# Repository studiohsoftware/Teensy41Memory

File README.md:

# Teensy41Memory
64MB SPI Memory Board for Teensy 4.1
</br>
https://oshpark.com/shared_projects/a06G97QZ
</br>

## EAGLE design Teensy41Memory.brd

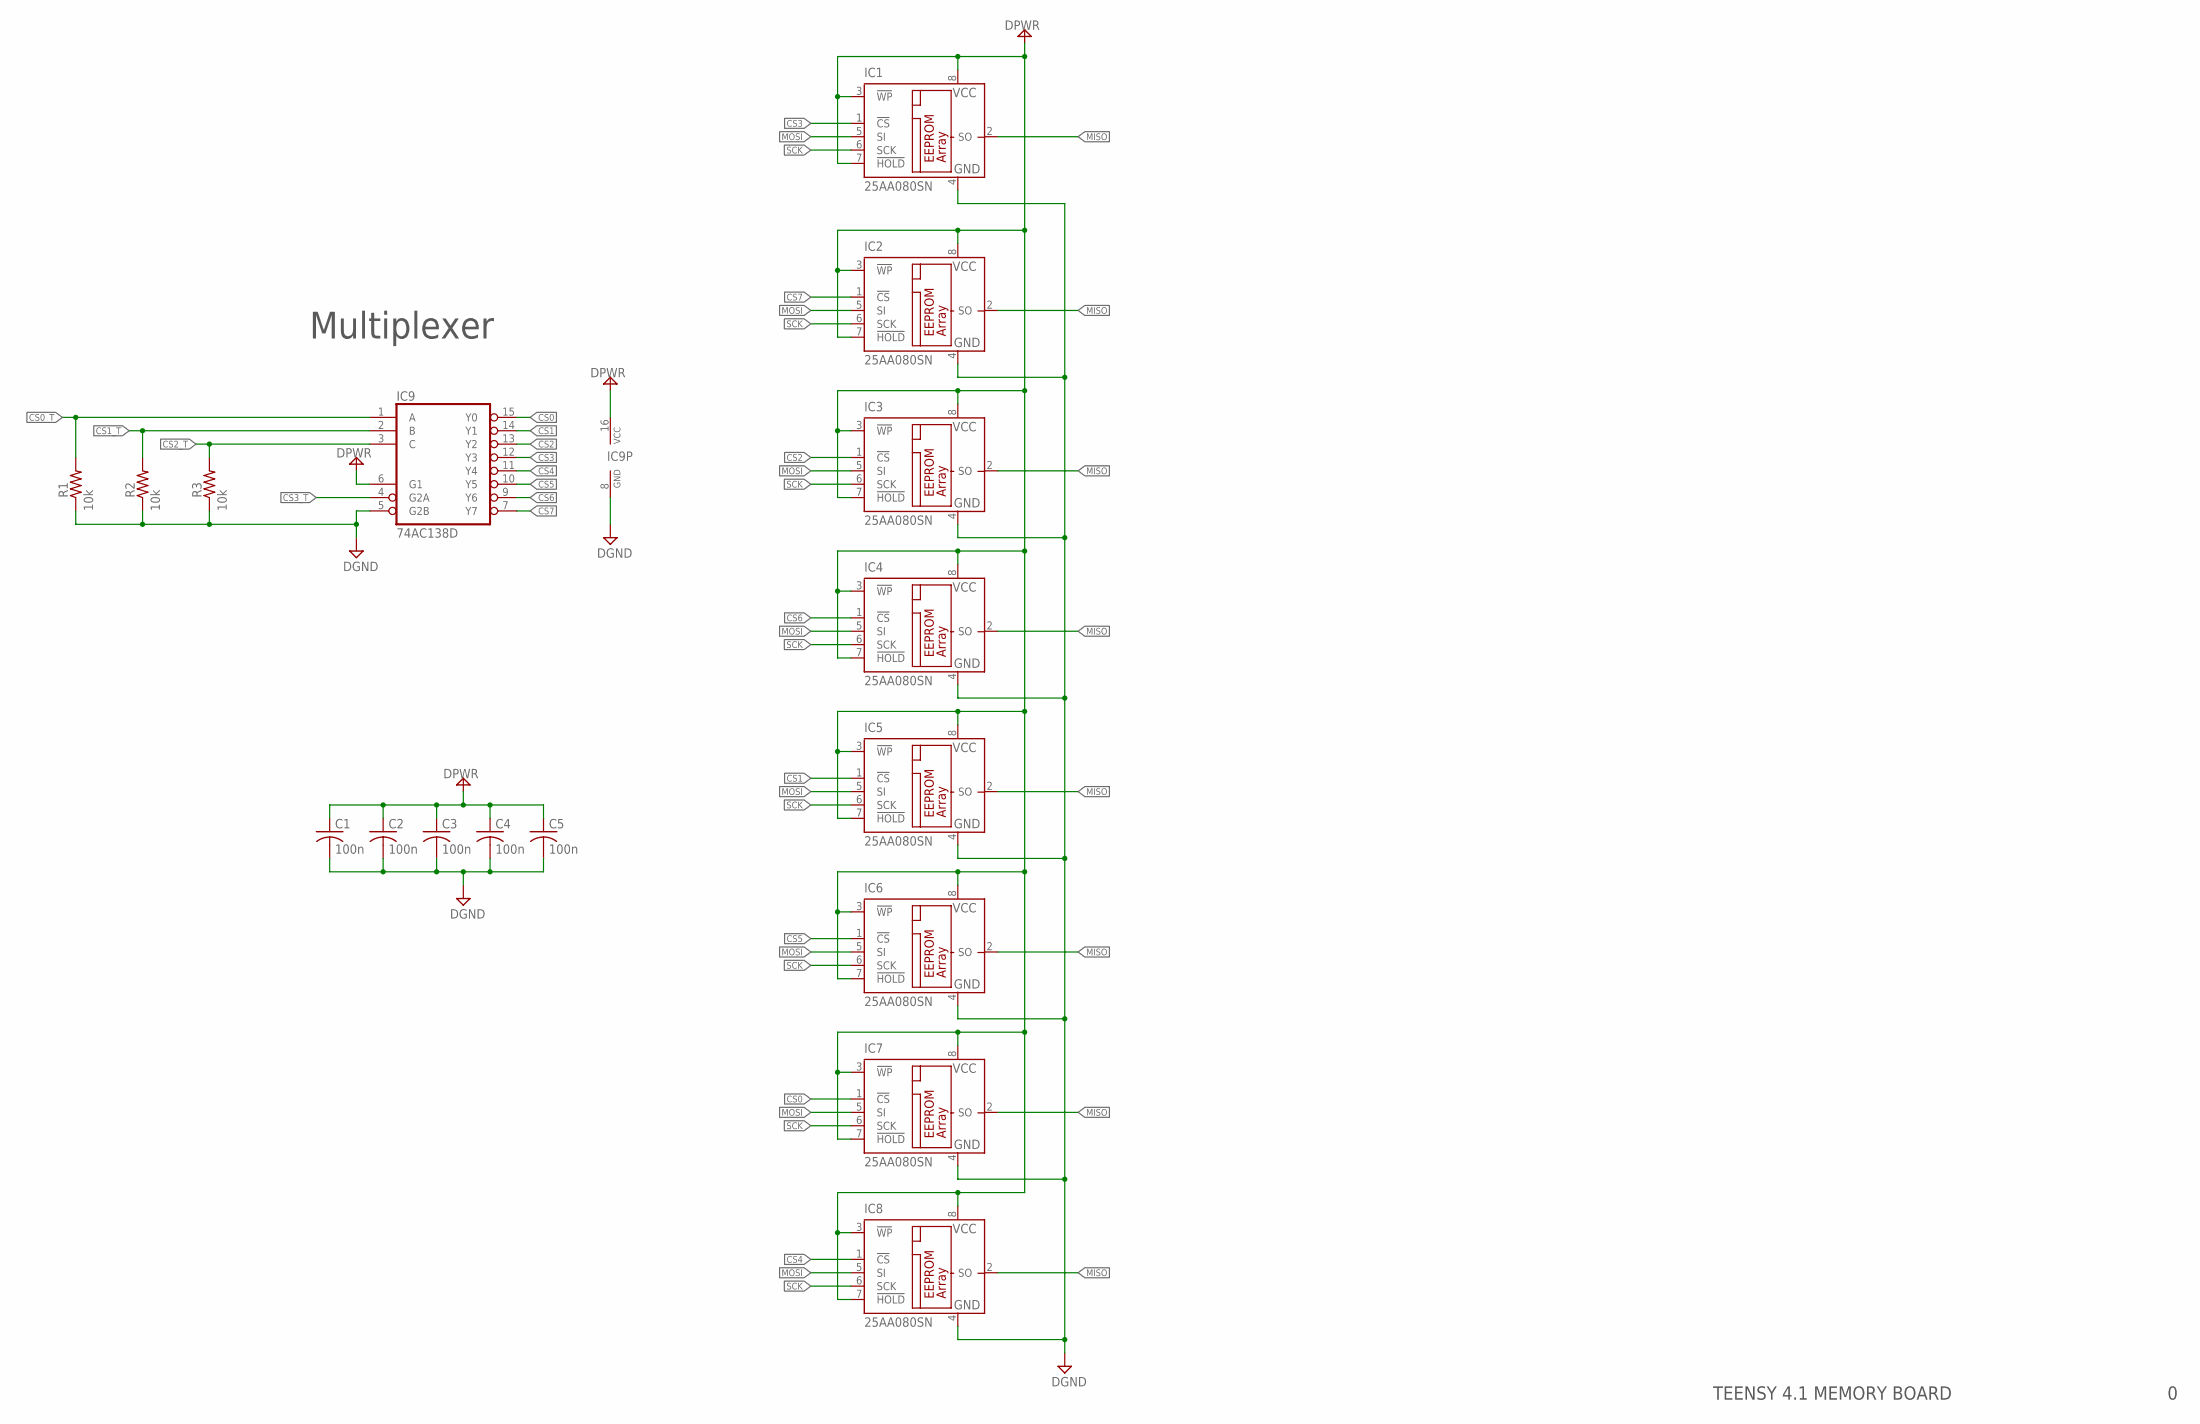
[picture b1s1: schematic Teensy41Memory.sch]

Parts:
C1, C2, C3, C4, C5: 100n; C0603
IC1, IC2, IC3, IC4, IC5, IC6, IC7, IC8: 25AA080SN; SO-08
IC9: 74AC138D; SO16
R1, R2, R3: 10k; R0603

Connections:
CS0: IC7.1 (!CS), IC9.15 (Y0)
CS0_T: IC9.1 (A), R1.2
CS1: IC5.1 (!CS), IC9.14 (Y1)
CS1_T: IC9.2 (B), R2.2
CS2: IC3.1 (!CS), IC9.13 (Y2)
CS2_T: IC9.3 (C), R3.2
CS3: IC1.1 (!CS), IC9.12 (Y3)
CS3_T: IC9.4 (G2A)
CS4: IC8.1 (!CS), IC9.11 (Y4)
CS5: IC6.1 (!CS), IC9.10 (Y5)
CS6: IC4.1 (!CS), IC9.9 (Y6)
CS7: IC2.1 (!CS), IC9.7 (Y7)
DGND: C1.2, C2.2, C3.2, C4.2, C5.2, IC1.4 (GND), IC2.4 (GND), IC3.4 (GND), IC4.4 (GND), IC5.4 (GND), IC6.4 (GND), IC7.4 (GND), IC8.4 (GND), IC9.5 (G2B), IC9.8 (GND), R1.1, R2.1, R3.1
DPWR: C1.1, C2.1, C3.1, C4.1, C5.1, IC1.3 (!WP), IC1.7 (!HOLD), IC1.8 (VCC), IC2.3 (!WP), IC2.7 (!HOLD), IC2.8 (VCC), IC3.3 (!WP), IC3.7 (!HOLD), IC3.8 (VCC), IC4.3 (!WP), IC4.7 (!HOLD), IC4.8 (VCC), IC5.3 (!WP), IC5.7 (!HOLD), IC5.8 (VCC), IC6.3 (!WP), IC6.7 (!HOLD), IC6.8 (VCC), IC7.3 (!WP), IC7.7 (!HOLD), IC7.8 (VCC), IC8.3 (!WP), IC8.7 (!HOLD), IC8.8 (VCC), IC9.6 (G1), IC9.16 (VCC)
MISO: IC1.2 (SO), IC2.2 (SO), IC3.2 (SO), IC4.2 (SO), IC5.2 (SO), IC6.2 (SO), IC7.2 (SO), IC8.2 (SO)
MOSI: IC1.5 (SI), IC2.5 (SI), IC3.5 (SI), IC4.5 (SI), IC5.5 (SI), IC6.5 (SI), IC7.5 (SI), IC8.5 (SI)
SCK: IC1.6 (SCK), IC2.6 (SCK), IC3.6 (SCK), IC4.6 (SCK), IC5.6 (SCK), IC6.6 (SCK), IC7.6 (SCK), IC8.6 (SCK)

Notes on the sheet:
Multiplexer
TEENSY 4.1 MEMORY BOARD

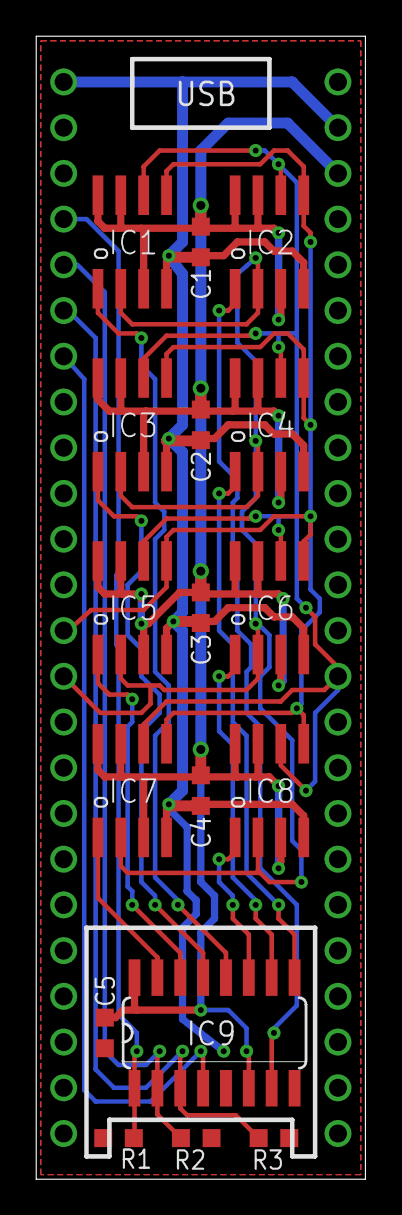
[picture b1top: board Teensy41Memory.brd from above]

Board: 2 copper layers, 18.3 x 63.5 mm, 275 parts (258 on the bottom side), 16 nets.

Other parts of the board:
U$1, U$8, U$10, U$17, U$27, U$38, U$140, U$144, U$151: A64CBI
U$2, U$11: W64CBI
U$3, U$12: V64CBI
U$4, U$5, U$13, U$14, U$25, U$34, U$124, U$131: E64CBI
U$6, U$15, U$39, U$75, U$135, U$146: S64CBI
U$7, U$16: H64CBI
U$9, U$18, U$123, U$130: P64CBI
U$19, U$28, U$118, U$125: M64CBI
U$20, U$29, U$99, U$119, U$126, U$142, U$145, U$153: O64CBI
U$21, U$24, U$30, U$33, U$120, U$127: D64CBI
U$22, U$31, U$137, U$148: I64CBI
U$23, U$32, U$41, U$77: N64CBI
U$26, U$35: X64CBI
U$36, U$37, U$155: B64CBI
U$40, U$76, U$122, U$129: Y64CBI
U$42, U$78, U$136, U$147: C64CBI
U$43, U$48, U$61, U$66, U$87, U$165, U$169, U$173, U$177: N64BI
U$44, U$47, U$54, U$62, U$65, U$68, U$92, U$96: O64BI
U$45, U$56, U$63, U$70: T64BI
U$46, U$64, U$84, U$86, U$91, U$103, U$112: E64BI
U$49, U$71: H64BI
U$50, U$72, U$88, U$101, U$104, U$110, U$113: A64BI
U$51, U$73, U$83: R64BI
U$52, U$74: D64BI
U$53, U$67, U$93, U$97: S64BI
U$55, U$69, U$107, U$116, U$162, U$170: F64BI
U$57, U$79: M54CBI
U$58, U$59, U$80, U$81: I54CBI
U$60, U$82: D54CBI
U$85, U$105, U$108, U$114, U$117, U$163, U$171: M64BI
U$89: B64BI
U$90: L64BI
U$94, U$98, U$166, U$174: C64BI
U$95: B54CBI
U$100, U$109: W64BI
U$102, U$111, U$167, U$175: V64BI
U$106, U$115: P64BI
U$121, U$128, U$141, U$152: T64CBI
U$132, U$133, U$156, U$157: CV-WHEEL-MED
U$134: A54CBI
U$138, U$139, U$149, U$150: L64CBI
U$143, U$154: R64CBI
U$158, U$160: CV-WHEEL-SM1
U$159, U$254: CV-WHEEL-LARGE
U$161: CV-WHEEL-SM2
U$164, U$168, U$172, U$176: I64BI
U$178, U$179, U$180, U$181, U$182, U$183, U$184, U$185, U$186, U$187, U$188, U$189, U$190, U$191, U$192, U$193, U$194, U$195, U$196, U$197, U$198, U$199, U$200, U$201, U$202, U$203, U$204, U$205, U$206, U$207, U$208, U$209, U$210, U$211, U$212, U$213, U$214, U$215, U$216, U$217, U$218, U$219, U$220, U$221, U$222, U$223, U$224, U$225, U$226, U$227, U$228, U$229, U$255, U$256: TARGET
U$230: D48CB
U$231: U48CB
U$232, U$240, U$249, U$252: A48CB
U$233, U$238, U$239, U$258: L48CB
U$234, U$242, U$246: O48CB
U$235: S48CB
U$236: C48CB
U$237: I48CB
U$241: T48CB
U$243, U$245, U$248: R48CB
U$244: P48CB
U$247: G48CB
U$250, U$251: M48CB
U$257: B48CB
U$259: E48CB

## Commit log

2023-03-10 Breakout pin 4 of 74AC138 to disable all CS
    It is now possible to set all eight chip selects HIGH on the output of 74AC138 by setting pin4 HIGH. The pin is available on Teensy 4.1 pin 5.
2023-03-10 Update OSH Park link to R1 project.
2023-03-10 Breakout pin 4 of 74AC138 to disable all CS
